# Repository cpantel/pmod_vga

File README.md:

# PMOD for VGA

kicad support files for hand made VGA PMODs

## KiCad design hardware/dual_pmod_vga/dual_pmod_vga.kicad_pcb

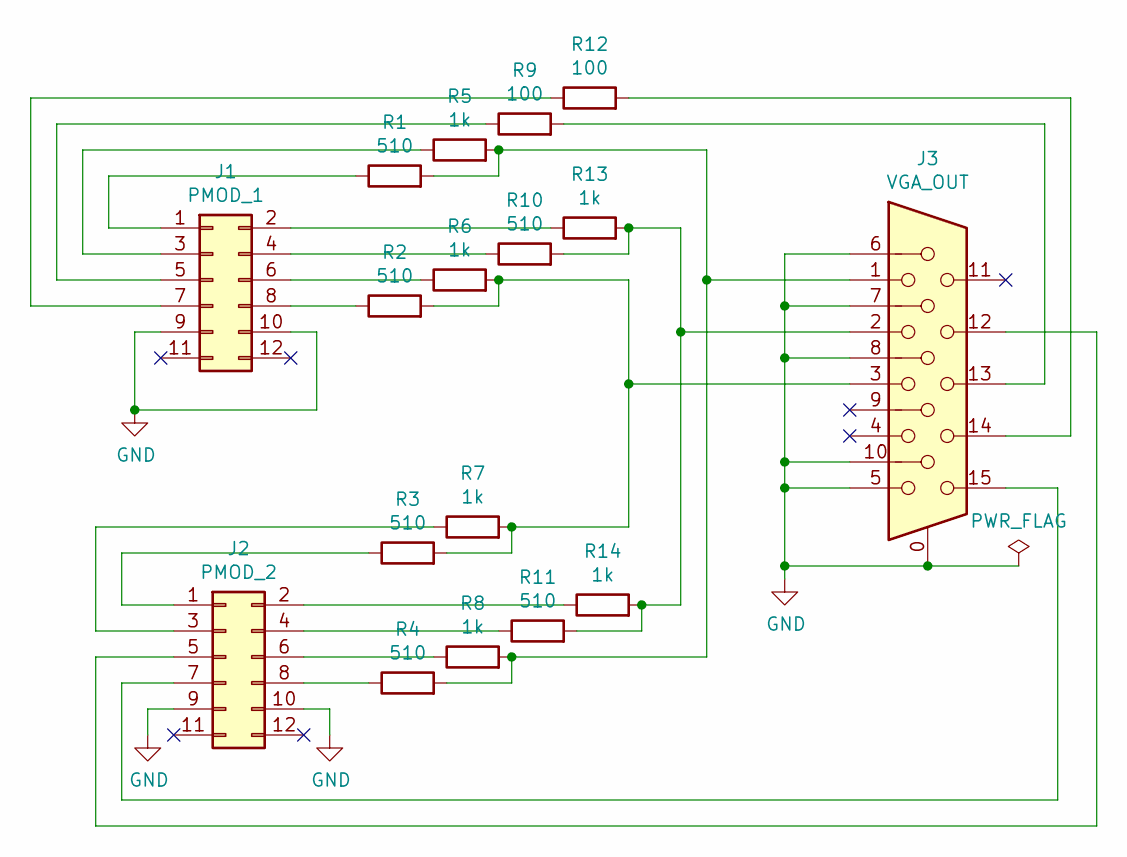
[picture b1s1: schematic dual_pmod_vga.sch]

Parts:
J1: PMOD_1; PinSocket_2x06_P1.27mm_Horizontal
J2: PMOD_2; PinSocket_2x06_P1.27mm_Horizontal
J3: VGA_OUT; DSUB-15-HD_Female_Horizontal_P2.29x1.98mm_EdgePinOffset8.35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
R1, R2, R3, R4, R10, R11: 510; R_Axial_DIN0204_L3.6mm_D1.6mm_P7.62mm_Horizontal
R5, R6, R7, R8, R13, R14: 1k; R_Axial_DIN0204_L3.6mm_D1.6mm_P7.62mm_Horizontal
R9, R12: 100; R_Axial_DIN0204_L3.6mm_D1.6mm_P7.62mm_Horizontal

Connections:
GND: J1.9, J1.10, J2.9, J2.10, J3.0, J3.5, J3.6, J3.7, J3.8, J3.10
unnamed: J1.1, R1.1
unnamed: J1.2, R13.1
unnamed: J1.3, R5.1
unnamed: J1.4, R10.1
unnamed: J1.5, R9.1
unnamed: J1.6, R6.1
unnamed: J1.7, R12.1
unnamed: J1.8, R2.1
unnamed: J2.1, R3.1
unnamed: J2.2, R14.1
unnamed: J2.3, R7.1
unnamed: J2.4, R11.1
unnamed: J2.5, J3.12
unnamed: J2.6, R8.1
unnamed: J2.7, J3.15
unnamed: J2.8, R4.1
unnamed: J3.1, R1.2, R4.2, R5.2, R8.2
unnamed: J3.2, R10.2, R11.2, R13.2, R14.2
unnamed: J3.3, R2.2, R3.2, R6.2, R7.2
unnamed: J3.13, R9.2
unnamed: J3.14, R12.2

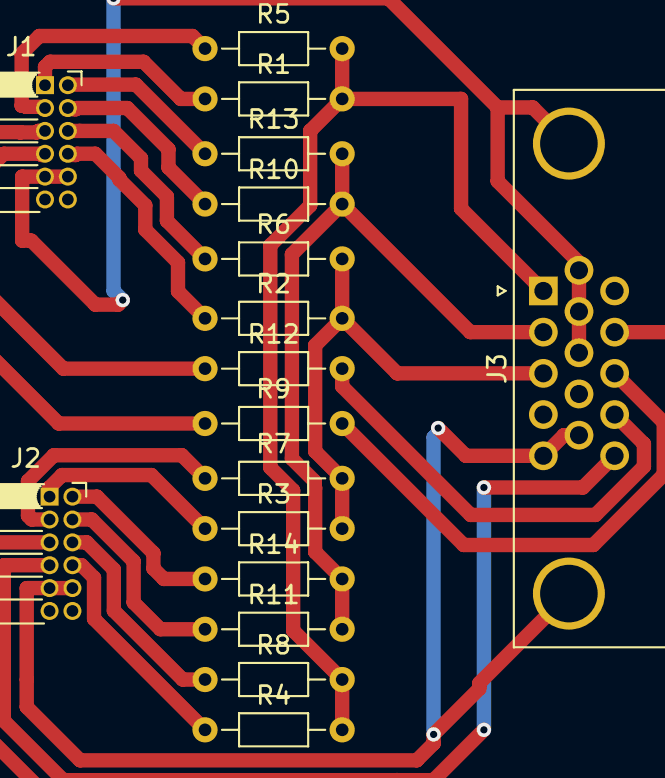
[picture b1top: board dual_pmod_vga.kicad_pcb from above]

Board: 2 copper layers, 17 parts (0 on the bottom side), 22 nets.

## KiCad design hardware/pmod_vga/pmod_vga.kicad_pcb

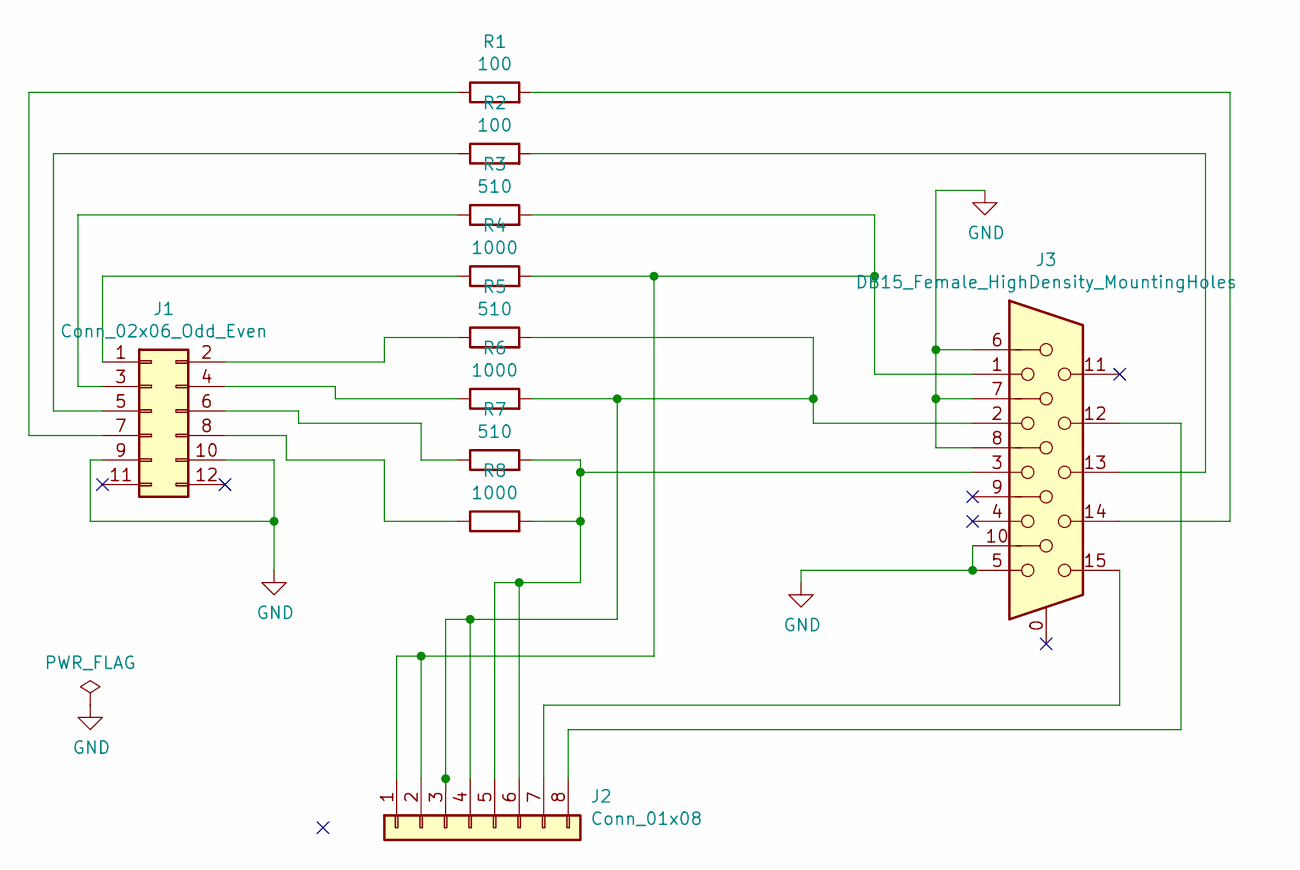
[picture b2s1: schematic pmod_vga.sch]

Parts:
J1: Conn_02x06_Odd_Even; PinHeader_2x06_P2.54mm_Vertical
J2: Conn_01x08; PinSocket_1x08_P2.54mm_Vertical
J3: DB15_Female_HighDensity_MountingHoles; DSUB-15-HD_Female_Horizontal_P2.29x1.98mm_EdgePinOffset8.35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
R1, R2: 100; R_Axial_DIN0204_L3.6mm_D1.6mm_P7.62mm_Horizontal
R3, R5, R7: 510; R_Axial_DIN0204_L3.6mm_D1.6mm_P7.62mm_Horizontal
R4, R6, R8: 1000; R_Axial_DIN0204_L3.6mm_D1.6mm_P7.62mm_Horizontal

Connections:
GND: J1.9, J1.10, J3.5, J3.6, J3.7, J3.8, J3.10
unnamed: J1.1, R4.1
unnamed: J1.2, R5.1
unnamed: J1.3, R3.1
unnamed: J1.4, R6.1
unnamed: J1.5, R2.1
unnamed: J1.6, R7.1
unnamed: J1.7, R1.1
unnamed: J1.8, R8.1
unnamed: J2.1, J2.2, J3.1, R3.2, R4.2
unnamed: J2.3, J2.4, J3.2, R5.2, R6.2
unnamed: J2.5, J2.6, J3.3, R7.2, R8.2
unnamed: J2.7, J3.15
unnamed: J2.8, J3.12
unnamed: J3.13, R2.2
unnamed: J3.14, R1.2

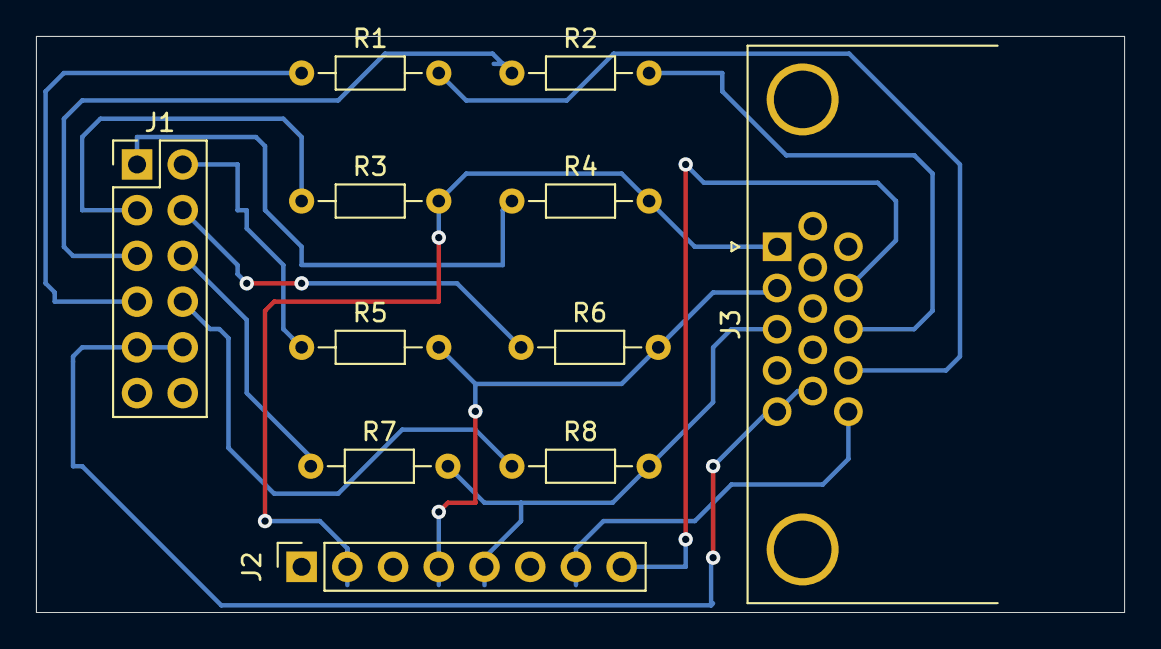
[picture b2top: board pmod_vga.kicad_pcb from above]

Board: 2 copper layers, 60.5 x 32.0 mm, 11 parts (0 on the bottom side), 16 nets.

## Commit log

2020-09-13 minor fixes
